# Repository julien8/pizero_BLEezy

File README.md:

# Bleezy: Raspberry Pi Zero BLE Module #

Using the nRF52188 a very interesting BLE solution for the Raspberry Pi is realized. The Raspberry Pi allows you to use OpenOCD to program the nRF chips ARM M0 core. This opens up potentioal for a variety of applications where Bluetooth can be used to monitor and control the state of the Raspberry Pi. 

*This project is licensed under the CERN OHL v1.2*

### Features ###

-nRF52188
-Coincell battery

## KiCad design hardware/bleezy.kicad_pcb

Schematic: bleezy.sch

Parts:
BT1: Coin Cell; keystone_3003
C1: 2.2uf; c_0402
C2: 1.0uf; c_0603
C3: 10uf; c_tant_B
C4, C7, C9, C10: 6pf; c_0402
C5, C14, C15: 100nf; c_0402
C6: 47nf; c_0402
C8: 2.2nf; c_0402
C11: 2.2pf; c_0402
C12: 1pf; c_0402
C13: 1.5pf; c_0402
C16: 1.0uf; c_0402
D1: D_Schottky_x2_KCom_KAA; sot23; Mouser Part No. 726-BAS7005E6327XT
D2: LED; Led_0603
IC1: NRF51822; pvqfn-n48
JP1: JUMPER; c_0603
L1: 4.7nH; inductor_smd_0402
L2: 10nH; inductor_smd_0402
L3: 3.3nH; inductor_smd_0402
L5: 10uH; inductor_smd_0603
L6: 15nH; inductor_smd_0402
P1: Analog Header; pin_strip_8
P2: Digital Con 2; pin_strip_8
P3: Raspberry_Pi_+_Conn; vasch_strip_20x2; Mouser Part No. 517-30340-6002
P5: Power Con; pin_strip_4
P6: TST; Ant_24ghz_small
R1, R2, R3: R; r_0402
U1: LD3985M33R; SOT-23-5
Y1: 32Khz; crystal_tc-38_horiz
Y2: 16Mhz; crystal_fa128

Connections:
+5V: C1.1, P5.4, R1.2, U1.1 (VIN), U1.3 (INH); also elsewhere on the board
/Back Power Protection/5V_MCU: P3.2 (VPP_(5v)), P3.4 (VPP_(5v)); also elsewhere on the board
/P0.00: IC1.4 (P0.00/AREF0), P1.1
/P0.01: IC1.5 (P0.01/AIN2), P1.2
/P0.02: IC1.6 (P0.02/AIN3), P1.3
/P0.03: IC1.7 (P0.03/AIN4), P1.4
/P0.04: IC1.8 (P0.04/AIN5), P1.5
/P0.05: IC1.9 (P0.05/AIN6), P1.6
/P0.06: IC1.10 (P0.06/AIN7/AREF1), P1.7
/P0.11: IC1.17 (P0.11), P2.2
/P0.12: IC1.16 (P0.10), P2.3
/P0.13: IC1.18 (P0.12), P2.1
/P0.21: IC1.40 (P0.21), P2.8
/P0.22: IC1.41 (P0.22), P2.7
/P0.23: IC1.42 (P0.23), P2.6
/P0.24: IC1.43 (P0.24), P2.5
/P0.25: IC1.44 (P0.25), P2.4
/PI_GPIO5: IC1.20 (P0.14), P3.29 (GPIO5)
/PI_GPIO6: IC1.19 (P0.13), P3.31 (GPIO6)
/PI_RXD: IC1.27 (P0.19), P3.10 (GPIO15/UART_RXD)
/PI_SPI_CE0: IC1.21 (P0.15), P3.24 (GPIO8/SPI_CE0)
/PI_SPI_MISO: IC1.25 (P0.17), P3.21 (GPIO9/SPI_MISO)
/PI_SPI_MOSI: IC1.26 (P0.18), P3.19 (GPIO10/SPI_M0SI)
/PI_SPI_SCLK: IC1.22 (P0.16), P3.23 (GPIO11/SPI_SCLK)
/PI_TXD: IC1.28 (P0.20), P3.8 (GPIO14/UART_TXD)
/VSense: IC1.3 (P0.30), R1.1, R2.1
/nRF_SWDCLK: IC1.24 (SWDCLK), P3.22 (GPIO25)
/nRF_SWDIO: IC1.23 (SWDIO/nRESET), P3.18 (GPIO24)
AVDD: C16.2, IC1.35 (AVDD), IC1.36 (AVDD), JP1.2, L6.1
GND: BT1.2, C1.2, C2.2, C3.2, C4.2, C5.2, C6.2, C7.2, C8.2, C9.2, C10.2, C12.1, C13.1, C14.2, C15.2, C16.1, IC1.13 (VSS), IC1.33 (VSS), IC1.34 (VSS), IC1.49 (EPAD), P1.8, P3.6 (GND), P3.9 (GND), P3.14 (GND), P3.20 (GND), P3.25 (GND), P3.30 (GND), P3.34 (GND), P3.39 (GND), P5.1, P5.2, R2.2, R3.2, U1.2 (GND); also elsewhere on the board
unnamed: BT1.1, C3.1, D1.2 (A)
unnamed: C2.1, D1.3 (A), U1.5 (VOUT)
unnamed: C4.1, IC1.46 (P0.27/AIN1/XL1), Y1.2
unnamed: C5.1, IC1.39 (DEC1)
unnamed: C6.1, IC1.29 (DEC2)
unnamed: C7.1, IC1.45 (P0.26/AIN0/XL2), Y1.1
unnamed: C8.1, IC1.30 (VDD_PA), L2.1
unnamed: C9.1, IC1.38 (XC2), Y2.2
unnamed: C10.1, IC1.37 (XC1), Y2.1
unnamed: C11.1, C12.2, L3.2
unnamed: C11.2, IC1.32 (ANT2), L1.2
unnamed: C13.2, L3.1, P6.1
unnamed: D2.1 (K), R3.1
unnamed: D2.2 (A), IC1.48 (P0.29)
unnamed: IC1.2 (DCC), L5.2
unnamed: IC1.31 (ANT1), L1.1, L2.2
unnamed: L5.1, L6.2
VCC: C14.1, C15.1, D1.1 (K), IC1.1 (VDD), IC1.12 (VDD), JP1.1, P5.3

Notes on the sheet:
Raspberry Pi Connection
nRF Bluetooth Module
Power Managment
Note: This device is designed without any type of warrenty or garuntee. This device has no radio conformance cerification for any country.
To Do: - setup the traces for better PCB routing - add gaurd ring to the crystal - add the DC/DC to the nRF module - make sheet bigger

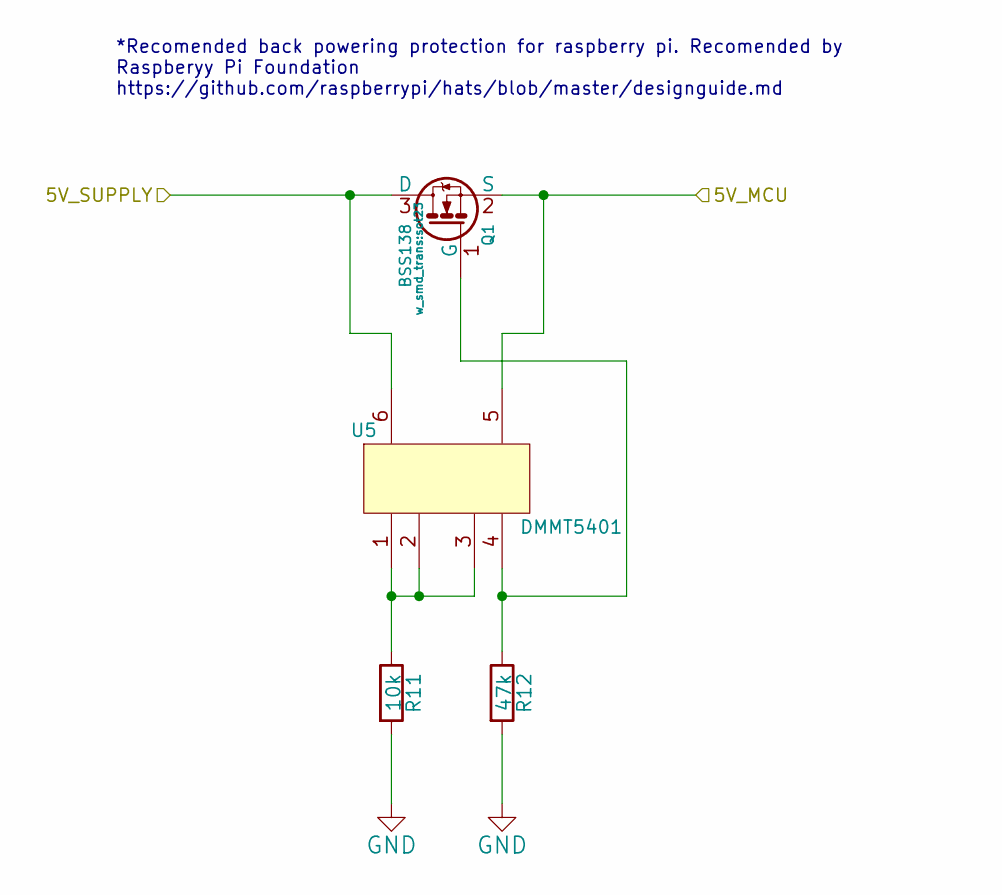
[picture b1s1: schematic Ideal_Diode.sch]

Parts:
Q1: BSS138; sot23; Mouser Part No. 621-DMG2305UX-13
R11: 10k; r_0402; Mouser Part No. 71-CRCW0402-10K-E3
R12: 47k; r_0402; Mouser Part No. 667-ERJ-2RKF4702X
U5: DMMT5401; sot23-6; Mouser Part No. 621-DMMT5401-7-F

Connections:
+5V: Q1.3 (D), U5.6; also elsewhere on the board
/Back Power Protection/5V_MCU: Q1.2 (S), U5.5; also elsewhere on the board
GND: R11.2, R12.2; also elsewhere on the board
unnamed: Q1.1 (G), R12.1, U5.4
unnamed: R11.1, U5.1, U5.2, U5.3

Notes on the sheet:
*Recomended back powering protection for raspberry pi. Recomended by Raspberyy Pi Foundation https://github.com/raspberrypi/hats/blob/master/designguide.md

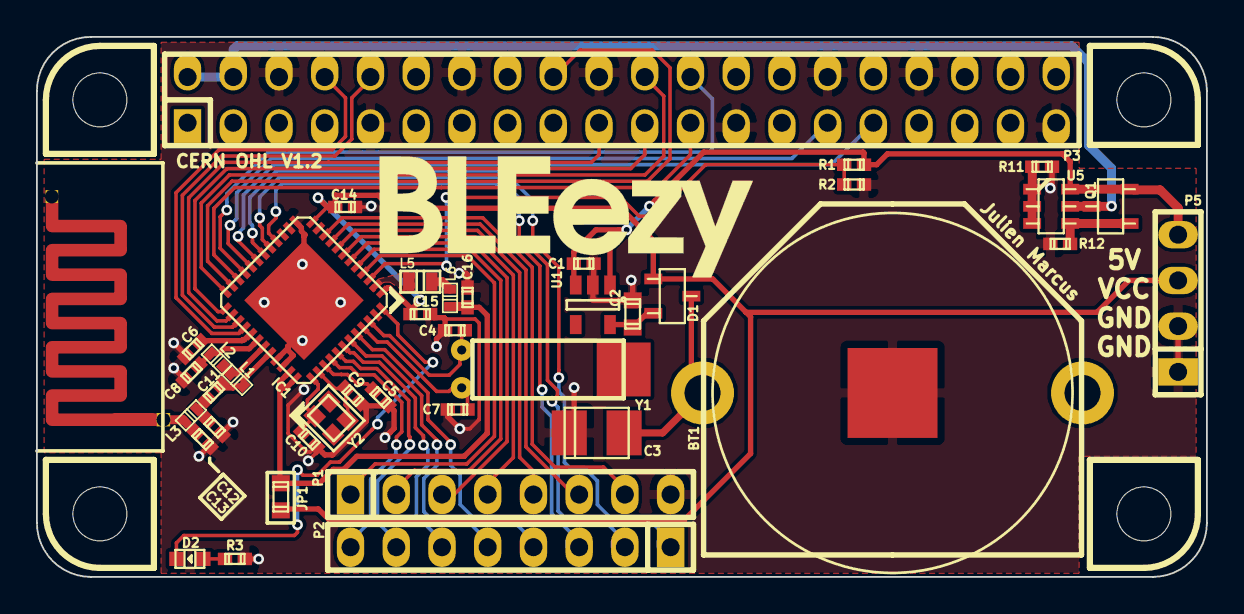
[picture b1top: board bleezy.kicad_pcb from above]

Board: 2 copper layers, 65.0 x 30.0 mm, 41 parts (0 on the bottom side), 50 nets.

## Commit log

2015-12-24 fixed a library link issue
2015-12-30 Initial commit of bleezy
2015-12-31 added LED and vsense net
2015-12-31 finished major component linking
2015-12-31 placed major components
2015-12-31 major group changes
2015-12-31 cleaned up schematic
2015-12-31 removed monolithic balun
2015-12-31 redid basic layout, some routing
2016-01-06 finished routing
2016-01-07 added some to do
2016-01-07 added DC/DC, changed some pinouts
2016-01-07 rerouted with new pinout and bat on top
2016-01-07 updates after re-routing
2016-01-07 Remove backup-files from git
    Also, create a .gitignore file to prevent it from happening again
2016-01-07 Updated PCB routing
    Mostly aesthetic changes...
    Beefed up a few power-lines.
    Added guard-rings around the crystals
    Made the B.Cu ground-plane contigous (although it has a narrow passage)
    Removed a lot of unncessary vias
2016-01-09 changed some silk labels
2016-01-09 inital commit of BOM complete, untested
2016-01-09 added part numbers to component feilds
2016-01-17 inital commit of installer script
2016-01-17 added some instructions

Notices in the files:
hardware/bleezy.kicad_pcb:
License: CERN OHL V1.2
